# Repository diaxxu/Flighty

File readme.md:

<svg width="100%" viewBox="0 0 680 160" xmlns="http://www.w3.org/2000/svg"><defs><mask id="imagine-text-gaps-1nc41s" maskUnits="userSpaceOnUse"><rect x="0" y="0" width="680" height="160" fill="white"/><rect x="60.694801330566406" y="23.187637329101562" width="558.6104125976562" height="111.06857299804688" fill="black" rx="2"/></mask></defs>

  <!-- Speed lines behind text — thin diagonal strokes, left to right, rising -->
  <g stroke="#5DCAA5" stroke-linecap="round" fill="none" style="fill:none;stroke:rgb(93, 202, 165);color:rgb(255, 255, 255);stroke-width:1px;stroke-linecap:round;stroke-linejoin:miter;opacity:1;font-family:&quot;Anthropic Sans&quot;, -apple-system, BlinkMacSystemFont, &quot;Segoe UI&quot;, sans-serif;font-size:16px;font-weight:400;text-anchor:start;dominant-baseline:auto">
    <line x1="60" y1="125" x2="190" y2="55" stroke-width="0.8" opacity="0.18" mask="url(#imagine-text-gaps-1nc41s)" style="fill:none;stroke:rgb(93, 202, 165);color:rgb(255, 255, 255);stroke-width:0.8px;stroke-linecap:round;stroke-linejoin:miter;opacity:0.18;font-family:&quot;Anthropic Sans&quot;, -apple-system, BlinkMacSystemFont, &quot;Segoe UI&quot;, sans-serif;font-size:16px;font-weight:400;text-anchor:start;dominant-baseline:auto"/>
    <line x1="70" y1="132" x2="220" y2="58" stroke-width="0.5" opacity="0.12" mask="url(#imagine-text-gaps-1nc41s)" style="fill:none;stroke:rgb(93, 202, 165);color:rgb(255, 255, 255);stroke-width:0.5px;stroke-linecap:round;stroke-linejoin:miter;opacity:0.12;font-family:&quot;Anthropic Sans&quot;, -apple-system, BlinkMacSystemFont, &quot;Segoe UI&quot;, sans-serif;font-size:16px;font-weight:400;text-anchor:start;dominant-baseline:auto"/>
    <line x1="50" y1="118" x2="170" y2="52" stroke-width="0.4" opacity="0.10" mask="url(#imagine-text-gaps-1nc41s)" style="fill:none;stroke:rgb(93, 202, 165);color:rgb(255, 255, 255);stroke-width:0.4px;stroke-linecap:round;stroke-linejoin:miter;opacity:0.1;font-family:&quot;Anthropic Sans&quot;, -apple-system, BlinkMacSystemFont, &quot;Segoe UI&quot;, sans-serif;font-size:16px;font-weight:400;text-anchor:start;dominant-baseline:auto"/>
    <line x1="460" y1="108" x2="640" y2="40" stroke-width="0.8" opacity="0.18" mask="url(#imagine-text-gaps-1nc41s)" style="fill:none;stroke:rgb(93, 202, 165);color:rgb(255, 255, 255);stroke-width:0.8px;stroke-linecap:round;stroke-linejoin:miter;opacity:0.18;font-family:&quot;Anthropic Sans&quot;, -apple-system, BlinkMacSystemFont, &quot;Segoe UI&quot;, sans-serif;font-size:16px;font-weight:400;text-anchor:start;dominant-baseline:auto"/>
    <line x1="470" y1="118" x2="648" y2="48" stroke-width="0.5" opacity="0.12" mask="url(#imagine-text-gaps-1nc41s)" style="fill:none;stroke:rgb(93, 202, 165);color:rgb(255, 255, 255);stroke-width:0.5px;stroke-linecap:round;stroke-linejoin:miter;opacity:0.12;font-family:&quot;Anthropic Sans&quot;, -apple-system, BlinkMacSystemFont, &quot;Segoe UI&quot;, sans-serif;font-size:16px;font-weight:400;text-anchor:start;dominant-baseline:auto"/>
    <line x1="455" y1="100" x2="630" y2="35" stroke-width="0.4" opacity="0.10" mask="url(#imagine-text-gaps-1nc41s)" style="fill:none;stroke:rgb(93, 202, 165);color:rgb(255, 255, 255);stroke-width:0.4px;stroke-linecap:round;stroke-linejoin:miter;opacity:0.1;font-family:&quot;Anthropic Sans&quot;, -apple-system, BlinkMacSystemFont, &quot;Segoe UI&quot;, sans-serif;font-size:16px;font-weight:400;text-anchor:start;dominant-baseline:auto"/>
  </g>

  <!-- Main wordmark -->
  <text x="340" y="112" text-anchor="middle" font-family="'Rajdhani', 'Arial Narrow', sans-serif" font-size="96" font-weight="700" letter-spacing="20" fill="#5DCAA5" style="fill:rgb(93, 202, 165);stroke:none;color:rgb(255, 255, 255);stroke-width:1px;stroke-linecap:butt;stroke-linejoin:miter;opacity:1;font-family:Rajdhani, &quot;Arial Narrow&quot;, sans-serif;font-size:96px;font-weight:700;text-anchor:middle;dominant-baseline:auto"></text>

  <!-- The "I" dot replaced by a small compass rose / crosshair -->
  <!-- crosshair sits over the letter I — centered around x≈340, but "I" is the 5th letter -->
  <!-- We use a tiny crosshair as a decorative accent above the wordmark -->
  <g transform="translate(340, 28)" style="fill:rgb(0, 0, 0);stroke:none;color:rgb(255, 255, 255);stroke-width:1px;stroke-linecap:butt;stroke-linejoin:miter;opacity:1;font-family:&quot;Anthropic Sans&quot;, -apple-system, BlinkMacSystemFont, &quot;Segoe UI&quot;, sans-serif;font-size:16px;font-weight:400;text-anchor:start;dominant-baseline:auto">
    <circle cx="0" cy="0" r="7" fill="none" stroke="#9FE1CB" stroke-width="1" style="fill:none;stroke:rgb(159, 225, 203);color:rgb(255, 255, 255);stroke-width:1px;stroke-linecap:butt;stroke-linejoin:miter;opacity:1;font-family:&quot;Anthropic Sans&quot;, -apple-system, BlinkMacSystemFont, &quot;Segoe UI&quot;, sans-serif;font-size:16px;font-weight:400;text-anchor:start;dominant-baseline:auto"/>
    <line x1="-12" y1="0" x2="12" y2="0" stroke="#9FE1CB" stroke-width="1" stroke-linecap="round" style="fill:rgb(0, 0, 0);stroke:rgb(159, 225, 203);color:rgb(255, 255, 255);stroke-width:1px;stroke-linecap:round;stroke-linejoin:miter;opacity:1;font-family:&quot;Anthropic Sans&quot;, -apple-system, BlinkMacSystemFont, &quot;Segoe UI&quot;, sans-serif;font-size:16px;font-weight:400;text-anchor:start;dominant-baseline:auto"/>
    <line x1="0" y1="-12" x2="0" y2="12" stroke="#9FE1CB" stroke-width="1" stroke-linecap="round" style="fill:rgb(0, 0, 0);stroke:rgb(159, 225, 203);color:rgb(255, 255, 255);stroke-width:1px;stroke-linecap:round;stroke-linejoin:miter;opacity:1;font-family:&quot;Anthropic Sans&quot;, -apple-system, BlinkMacSystemFont, &quot;Segoe UI&quot;, sans-serif;font-size:16px;font-weight:400;text-anchor:start;dominant-baseline:auto"/>
    <circle cx="0" cy="0" r="2" fill="#5DCAA5" style="fill:rgb(93, 202, 165);stroke:none;color:rgb(255, 255, 255);stroke-width:1px;stroke-linecap:butt;stroke-linejoin:miter;opacity:1;font-family:&quot;Anthropic Sans&quot;, -apple-system, BlinkMacSystemFont, &quot;Segoe UI&quot;, sans-serif;font-size:16px;font-weight:400;text-anchor:start;dominant-baseline:auto"/>
  </g>

  <!-- Thin underline with notch — like a runway -->
  <line x1="80" y1="128" x2="600" y2="128" stroke="#1D9E75" stroke-width="1" opacity="0.5" mask="url(#imagine-text-gaps-1nc41s)" style="fill:rgb(0, 0, 0);stroke:rgb(29, 158, 117);color:rgb(255, 255, 255);stroke-width:1px;stroke-linecap:butt;stroke-linejoin:miter;opacity:0.5;font-family:&quot;Anthropic Sans&quot;, -apple-system, BlinkMacSystemFont, &quot;Segoe UI&quot;, sans-serif;font-size:16px;font-weight:400;text-anchor:start;dominant-baseline:auto"/>
  <line x1="316" y1="128" x2="364" y2="128" stroke="#9FE1CB" stroke-width="2.5" stroke-linecap="round" opacity="0.9" mask="url(#imagine-text-gaps-1nc41s)" style="fill:rgb(0, 0, 0);stroke:rgb(159, 225, 203);color:rgb(255, 255, 255);stroke-width:2.5px;stroke-linecap:round;stroke-linejoin:miter;opacity:0.9;font-family:&quot;Anthropic Sans&quot;, -apple-system, BlinkMacSystemFont, &quot;Segoe UI&quot;, sans-serif;font-size:16px;font-weight:400;text-anchor:start;dominant-baseline:auto"/>

  <!-- Tiny dots at ends of underline -->
  <circle cx="80" cy="128" r="2" fill="#1D9E75" opacity="0.5" style="fill:rgb(29, 158, 117);stroke:none;color:rgb(255, 255, 255);stroke-width:1px;stroke-linecap:butt;stroke-linejoin:miter;opacity:0.5;font-family:&quot;Anthropic Sans&quot;, -apple-system, BlinkMacSystemFont, &quot;Segoe UI&quot;, sans-serif;font-size:16px;font-weight:400;text-anchor:start;dominant-baseline:auto"/>
  <circle cx="600" cy="128" r="2" fill="#1D9E75" opacity="0.5" style="fill:rgb(29, 158, 117);stroke:none;color:rgb(255, 255, 255);stroke-width:1px;stroke-linecap:butt;stroke-linejoin:miter;opacity:0.5;font-family:&quot;Anthropic Sans&quot;, -apple-system, BlinkMacSystemFont, &quot;Segoe UI&quot;, sans-serif;font-size:16px;font-weight:400;text-anchor:start;dominant-baseline:auto"/>
</svg>

**Flighty** is my very first custom-designed flight controller! I built this to be a versatile "brain" for just about anything that flies, from standard quadcopters and fixed-wing UAVs to high-power model rockets.

I am currently using this board to power my personal RC VTOL project. It’s designed to be easy to solder (THT components), easy to repair, and a great hands-on project for anyone interested in PCB assembly.

##  Key Features

* **7x Servo/PWM Channels:** Plenty of outputs for complex RC planes, hexacopters, or VTOL transitions.
* **Rocketry Ready:** Two dedicated channels can be configured as electronic igniters (pyro-channels) for rocket motor ignition or parachute deployment.
* **Blackbox Data Logging:** Integrated **MicroSD slot** to record high-speed flight data, allowing you to re-analyze crashes or tune PID loops with precision.
* **Reliable Power Management:** Designed for **2S LiPo/Li-ion** setups with an integrated charging and protection circuit.
* **Repair-Friendly Design:** Focused on Through-Hole Technology (THT) for connectors and key components, making it durable and easy to fix in the field.

##  Hardware

* **Brain (MCU): STM32F405RGT6** – This is the heart of the board. It’s a powerful chip that handles high-frequency flight loops and complex navigation without breaking a sweat.
* **Gyro/Accel: MPU6500** – To keep things stable, I'm using the MPU6500 over I2C. It supports fast refresh rates (up to 500Hz on the bus) to keep the flight feeling smooth and responsive.
* **Altitude (Baro): BMP580** – This sensor is a beast. It’s incredibly precise, detecting altitude changes down to a few centimeters. It's perfect for a rock-steady hover or timing a rocket's parachute deployment at exactly the right moment.
* **Power: TPS63070 (Buck-Boost)** – I wanted to avoid brownouts. This regulator keeps a rock-solid 5V supplied to the sensors and MCU, even if the battery voltage drops during a hard maneuver.
* **Charging: BQ25883** – I added a built-in 2S balancer/charger. This is super convenient because you can top up your batteries directly through the board using the USB port.
* **Plug: USB Type-C** – Because nobody wants to carry around old Micro-USB cables anymore. One cable for your phone, your laptop, and your flight controller.

##  Software & Firmware

Flighty is compatible with **Ardupilot**, **INAV**, and **Betaflight**. 

> **Note:** Because this is a custom hardware layout, you will need to define a custom target (mapping the SPI/UART/PWM pins) in your chosen firmware.

---

##  Gallery

### Schematics

### PCB Design

### 3D Visuals

---

##  Bill of Materials (BOM)

| Item | Description | Quantity | Unit Price |
| :--- | :--- | :--- | :--- |
| **Flight Controller PCB** | Bare PCB from JLCPCB | 5 | $2.00 |
| **Flight Controller PCBA** | Fully Assembled Board | 2 | $130.71 |

**Project Total: $159.21**

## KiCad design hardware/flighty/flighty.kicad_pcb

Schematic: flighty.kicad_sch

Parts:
C1: 1uF; C_0805_2012Metric
C2, C3, C5, C8, C12, C13, C14, C18: 10uF; CP_Radial_D5.0mm_P2.00mm
C4: 47uF; CP_Radial_D8.0mm_P5.00mm
C6: 44uF; CP_Radial_D8.0mm_P5.00mm
C7, C15, C19, C30: 100nF; C_0805_2012Metric
C9, C10, C11, C16, C17: 22uF; CP_Radial_D5.0mm_P2.00mm
C20, C31, C32, C33, C34, C35: 100nF; C_0603_1608Metric
C21, C22: 0.1uF; C_0603_1608Metric
C23: 0.1uF; C_0805_2012Metric
C24, C25: 2.2uF; CP_Radial_D4.0mm_P1.50mm
C26, C27, C28: 1uf; C_0805_2012Metric
C29: 10uf; CP_Radial_D5.0mm_P2.00mm
C36, C37: 6.8pF; C_0805_2012Metric
Card1: TF-01A; TF-SMD_TF-01A; LCSC Part C91145
D1: LED; LED_0603_1608Metric
J1: Screw_Terminal_01x02; TerminalBlock_Xinya_XY308-2.54-2P_1x02_P2.54mm_Horizontal
J2, J3, J4, J5, J6, J7, J8: Conn_01x03; PinHeader_1x03_P2.54mm_Vertical
L1: 1uH; L_0805_2012Metric
L2: 1.5uh; L_0805_2012Metric
L3: 5.6uH; L_0805_2012Metric
L4: FCM1608KF-601T03; L0603; LCSC Part C141723
R2, R3: 5.1k; R_0603_1608Metric
R4, R8, R9, R10, R11, R12, R24: 10k; R_0603_1608Metric
R5, R13, R18, R19, R20, R21, R22, R23: 10K; R_0603_1608Metric
R6: 30.1k; R_0603_1608Metric
R7: 5.23k; R_0603_1608Metric
R14: 100k; R_0603_1608Metric
R15: 22.1k; R_0603_1608Metric
R16, R17: 4.7 k; R_0603_1608Metric
RR1: 383; R_0603_1608Metric
SW1, SW2: SW_Push; SW_PUSH_6mm
U1: MPU6500; QFN-24_L3.0-W3.0-P0.40-BL-EP; LCSC Part C50278
U3: TPS63070RNMR; VQFN-15_L3.0-W2.5-P0.50-BL; LCSC Part C109322
U4: BMP580; LGA-10_L2.0-W2.0-P0.50-TL_BMP580; LCSC Part C22391138
U5: BQ25883RGER; VFQFPN-24_L4.0-W4.0-P0.50-BL-EP2.8; LCSC Part C544362
U6: LMR51430YFDDCR; SOT-23-6_L2.9-W1.6-P0.95-LS2.9-BL; LCSC Part C5219261
U7: STM32F405RGTx; LQFP-64_10x10mm_P0.5mm
USB1: TYPE-C 16PIN 2MD(073); USB-C-SMD_TYPE-C-6PIN-2MD-073; LCSC Part C2765186
X1: X322512MSB4SI; CRYSTAL-SMD_4P-L3.2-W2.5-BL; LCSC Part C9002
X2: Q13FC1350000400; FC-135R_L3.2-W1.5; LCSC Part C32346

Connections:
+3.3V: C16.1, C17.1, C19.1, C20.1, C21.2, C22.2, C26.1, C27.1, C28.1, C29.1, C30.1, C31.1, C32.1, C33.1, C34.1, Card1.4 (VDD), L3.2, L4.2, R16.1, R17.1, R18.1, R19.1, R20.1, R21.1, R22.1, R23.1, SW2.2, U1.8 (VDDIO), U1.9 (SDO/AD0), U1.13 (VDD), U1.22 (nCS), U4.1 (VDDIO), U4.10 (VDD), U7.1 (VBAT), U7.19 (VDD), U7.32 (VDD), U7.48 (VDD), U7.64 (VDD)
+5V: C8.2, C9.2, C10.2, C11.2, J2.2, J3.2, J4.2, J5.2, J6.2, J7.2, J8.2, R5.2, R8.1, U3.5 (FB), U3.7 (Vout), U3.8 (Vout)
+BATT: C5.1, J1.1, U5.13 (BAT), U5.14 (BAT)
/BMP_INT: U4.7 (INT), U7.36 (PB15)
/BMP_SCL: U4.2 (SCK), U7.58 (PB6)
/BMP_SDA: U4.4 (SDI), U7.59 (PB7)
/BQ_CE: U5.3 (~CE), U7.37 (PC6)
/BQ_INT: R10.2, U5.6 (~INT), U7.38 (PC7)
/BQ_PG: R8.2, U5.9 (~PG)
/BQ_SCL: R11.2, U5.5 (SCL)
/BQ_SDA: R12.2, U5.4 (SDA)
/BTST: C4.1, L1.2, U5.17 (SW), U5.18 (SW)
/MPU_INT: U1.12 (INT), U7.35 (PB14)
/MPU_SCL: R17.2, U1.23 (SCL/SCLK), U7.29 (PB10)
/MPU_SDA: R16.2, U1.24 (SDA/SDI), U7.30 (PB11)
/SD_CD: Card1.9 (CD)
/SD_CLK: Card1.5 (CLK(SCLK)), R23.2, U7.53 (PC12)
/SD_CMD: Card1.3 (CMD(DI)), R22.2, U7.54 (PD2)
/SD_DAT0: Card1.7 (DAT0(D0)), R21.2, U7.39 (PC8)
/SD_DAT1: Card1.8 (DAT1(RSV)), R20.2, U7.40 (PC9)
/SD_DAT2: Card1.1 (DAT2(RSV)), R19.2, U7.51 (PC10)
/SD_DAT3: Card1.2 (CDDAT3(CS)), R18.2, U7.52 (PC11)
/SERVO_1: J3.1, U7.61 (PB8)
/SERVO_2: J2.1, U7.62 (PB9)
/SERVO_3: J4.1, U7.55 (PB3)
/SERVO_4: J5.1, U7.16 (PA2)
/SERVO_5: J6.1, U7.17 (PA3)
/SERVO_6: J7.1, U7.21 (PA5)
/SERVO_7: J8.1, U7.22 (PA6)
/USB_DN: U7.44 (PA11), USB1.5 (DN2), USB1.7 (DN1)
/USB_DP: U7.45 (PA12), USB1.6 (DP1), USB1.8 (DP2)
/USB_vbus: USB1.2 (VBUS), USB1.11 (VBUS)
GND: C2.2, C3.2, C5.2, C6.2, C7.1, C8.1, C9.1, C10.1, C11.1, C12.1, C13.1, C14.1, C16.2, C17.2, C18.2, C19.2, C20.2, C21.1, C22.1, C23.1, C24.1, C25.1, C26.2, C27.2, C28.2, C29.2, C30.2, C31.2, C32.2, C33.2, C34.2, C36.1, C37.2, Card1.6 (VSS), Card1.10 (GND), Card1.11 (GND), J2.3, J3.3, J4.3, J5.3, J6.3, J7.3, J8.3, R2.1, R3.1, R4.2, R6.2, R15.2, R24.1, RR1.2, SW1.1, U1.11 (FSYNC), U1.18 (GND), U3.4 (GND), U3.6 (FB2), U3.10 (PGND), U3.15 (Vsel), U4.3 (VSS), U4.5 (SDO), U4.6 (CSB), U4.8 (VSS), U4.9 (VSS), U5.19 (GND), U5.20 (GND), U6.1 (GND), U7.12 (VSSA), U7.18 (VSS), U7.63 (VSS), USB1.1 (GND), USB1.12 (GND), USB1.13 (SHELL), USB1.14 (SHELL), X1.2 (GND), X1.4 (GND)
unnamed: C2.1, L1.1, U5.21 (PMID), U5.22 (PMID)
unnamed: C35.1, SW1.2
unnamed: D1.2 (A), R9.1
unnamed: D1.1 (K), U5.2 (STAT)
unnamed: R9.2, R10.1, R11.1, R12.1
unnamed: C23.2, U1.10 (REGOUT)
unnamed: R13.1, U3.1 (PS/SYNC), U3.14 (EN)
unnamed: L2.1, U3.11 (L1)
unnamed: L2.2, U3.9 (L2)
unnamed: R5.1, U3.2 (PG)
unnamed: C7.2, U3.3 (Vaux)
unnamed: C4.2, U5.12 (BTST)
unnamed: RR1.1, U5.8 (ILIM)
unnamed: R4.1, R6.1, R7.2, U5.7 (TS)
unnamed: C15.2, U6.6 (CB)
unnamed: R14.2, R15.1, U6.4 (FB)
unnamed: C15.1, L3.1, R14.1, U6.2 (SW)
unnamed: R24.2, SW2.1, U7.60 (BOOT0)
unnamed: C35.2, U7.7 (NRST)
unnamed: C37.1, U7.3 (PC14), X2.1
unnamed: C36.2, U7.4 (PC15), X2.2
unnamed: U7.5 (PH0), X1.1 (OSC1)
unnamed: U7.6 (PH1), X1.3 (OSC2)
unnamed: C24.2, U7.31 (VCAP_1)
unnamed: C25.2, U7.47 (VCAP_2)
unnamed: L4.1, U7.13 (VDDA)
unnamed: R3.2, USB1.4 (CC1)
unnamed: R2.2, USB1.10 (CC2)
PGND: C1.1, J1.2, U5.25 (EP)
VREGN: C3.1, R7.1, U5.11 (REGN)
VSYS: C6.1, C12.2, C13.2, C14.2, C18.1, R13.2, U3.12 (Vin), U3.13 (Vin), U5.16 (SYS), U6.3 (VIN), U6.5 (EN)
vbus: C1.2, U5.23 (VBUS)

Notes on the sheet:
flight controller

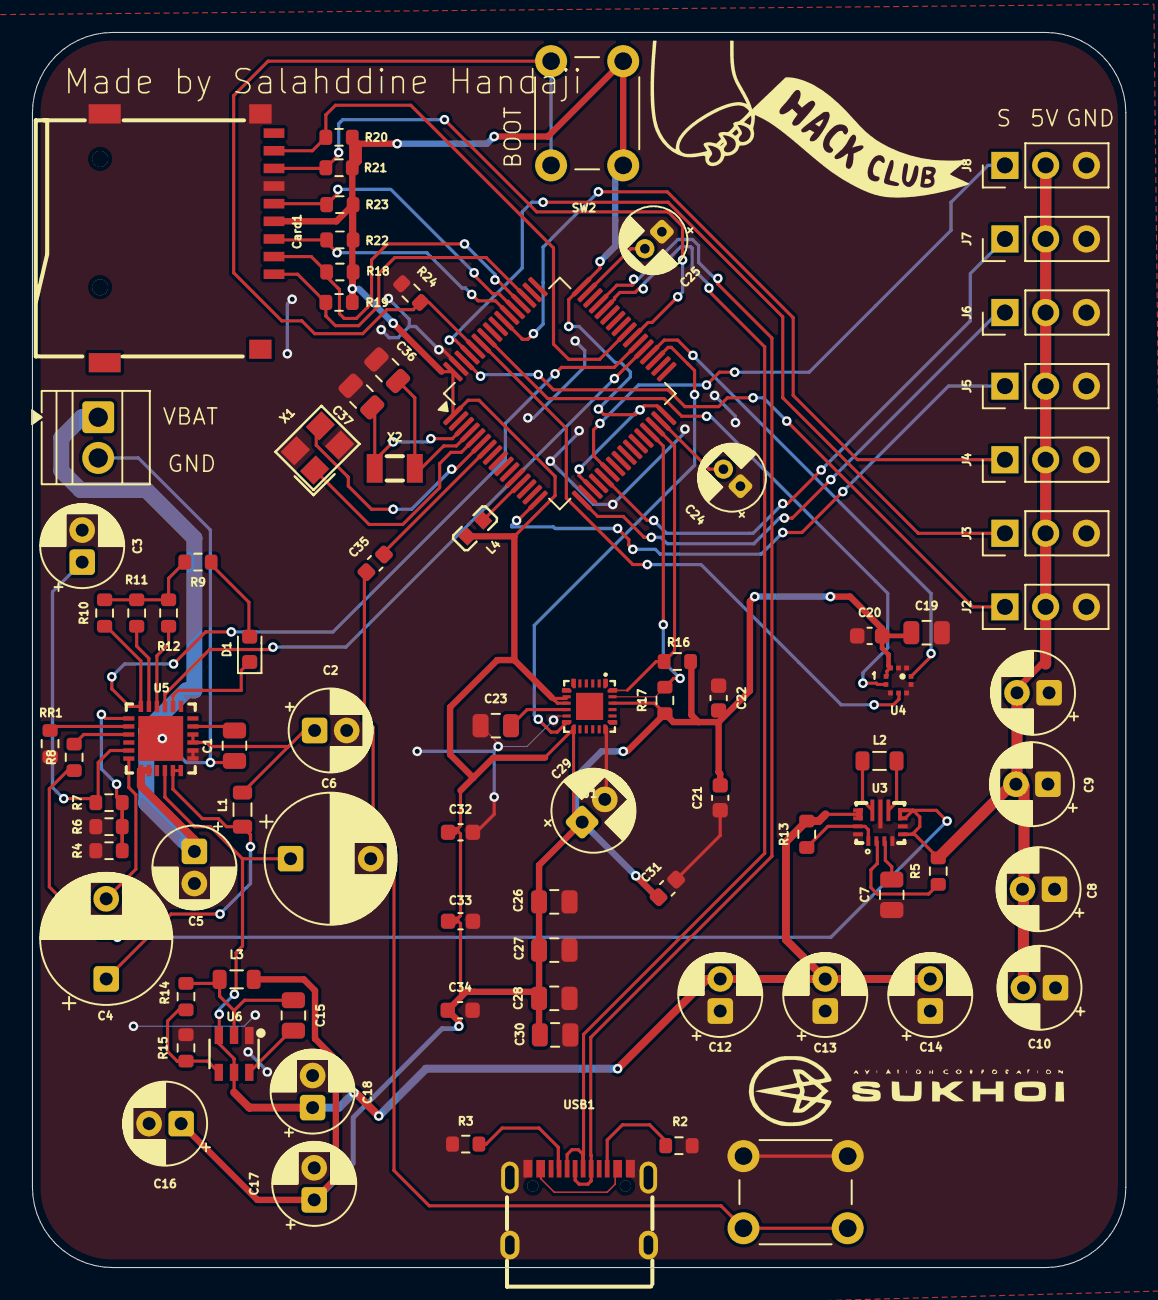
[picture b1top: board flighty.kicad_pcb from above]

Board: 2 copper layers, 68.2 x 77.0 mm, 86 parts (0 on the bottom side), 64 nets.

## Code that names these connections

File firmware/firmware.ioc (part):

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Mcu.Name=STM32F405RGTx
Mcu.Package=LQFP64
Mcu.UserName=STM32F405RGTx
PA11.Mode=Device_Only
PA11.Signal=USB_OTG_FS_DM
PA12.Mode=Device_Only
PA12.Signal=USB_OTG_FS_DP
PA13.Mode=Serial_Wire
PA13.Signal=SYS_JTMS-SWDIO
PA14.Mode=Serial_Wire
PA14.Signal=SYS_JTCK-SWCLK
PA2.Signal=S_TIM2_CH3
PA3.Signal=S_TIM2_CH4
PA5.Signal=S_TIM2_CH1_ETR
PA6.Signal=S_TIM13_CH1
PB10.Mode=I2C
PB10.Signal=I2C2_SCL
PB11.Mode=I2C
PB11.Signal=I2C2_SDA
PB13.GPIOParameters=GPIO_Label
PB13.GPIO_Label=SD_DET
PB13.Signal=GPIO_Input
PB14.GPIOParameters=GPIO_Label
PB14.GPIO_Label=MPU_INT
PB14.Signal=GPXTI14
PB15.GPIOParameters=GPIO_Label
PB15.GPIO_Label=BMP_INT
PB15.Signal=GPXTI15
PB3.Signal=S_TIM2_CH2
PB6.Mode=I2C
PB6.Signal=I2C1_SCL
PB7.Mode=I2C
PB7.Signal=I2C1_SDA
PB8.Signal=S_TIM10_CH1
PB9.Signal=S_TIM11_CH1
PC10.Mode=SD_4_bits_Wide_bus
PC10.Signal=SDIO_D2
PC11.Mode=SD_4_bits_Wide_bus
PC11.Signal=SDIO_D3
PC12.Mode=SD_4_bits_Wide_bus
PC12.Signal=SDIO_CK
PC14-OSC32_IN.Mode=LSE-External-Oscillator
PC14-OSC32_IN.Signal=RCC_OSC32_IN
PC15-OSC32_OUT.Mode=LSE-External-Oscillator
PC15-OSC32_OUT.Signal=RCC_OSC32_OUT
PC6.GPIOParameters=GPIO_Label
PC6.GPIO_Label=BQ_CE
PC6.Signal=GPIO_Output
PC7.GPIOParameters=GPIO_Label
PC7.GPIO_Label=BQ_INT
PC7.Signal=GPXTI7
PC8.Mode=SD_4_bits_Wide_bus
PC8.Signal=SDIO_D0
PC9.Mode=SD_4_bits_Wide_bus
PC9.Signal=SDIO_D1
PD2.Mode=SD_4_bits_Wide_bus
PD2.Signal=SDIO_CMD
PH0-OSC_IN.Mode=HSE-External-Oscillator
PH0-OSC_IN.Signal=RCC_OSC_IN
PH1-OSC_OUT.Mode=HSE-External-Oscillator
PH1-OSC_OUT.Signal=RCC_OSC_OUT
RCC.HSE_VALUE=25000000
RCC.SYSCLKFreq_VALUE=16000000
board=custom
